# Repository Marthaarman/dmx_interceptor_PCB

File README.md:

# PCB DMX Interceptor
A PCB designed for the dmx-transceiver library, to which an extra switch can be connected.
https://github.com/Marthaarman/dmx-transceiver

schematics: https://github.com/Marthaarman/dmx_interceptor_PCB/blob/main/dmx_interceptor.pdf

## components
- 2x debo rs485 TTL - https://www.reichelt.de/de/en/developer-boards-ttl-to-rs485-max485-debo-rs485-ttl-p282703.html
- 1x arduino pro mini - https://www.digikey.nl/nl/products/detail/sparkfun-electronics/DEV-11113/5140820
- 2x 3 pin screw terminal - https://www.digikey.nl/nl/products/detail/cui-devices/TB009-508-03BE/10064152
- 2x 2 pin screw terminal - https://www.digikey.nl/nl/products/detail/cui-devices/TB009-508-02BE/10064151
- 1x 10k resistor 0603 (1608 metric) - https://www.digikey.nl/nl/products/detail/stackpole-electronics-inc/RNCP0603FTD10K0/2240139
- 2x 12 pin header female - https://www.digikey.nl/nl/products/detail/adam-tech/RS1-12-G/9832041
- 4x 4 pin header female - https://www.digikey.nl/nl/products/detail/adam-tech/RS1-04-G/9829303
- 2x 12 pin header male - https://www.digikey.nl/nl/products/detail/adam-tech/PH1-12-UA/9830395

Depending on the FT232RL you bought you need either male or female:
- 1x female 5 pin header for ft232rl adapter: https://www.digikey.nl/nl/products/detail/adam-tech/RS1-05-G/9832046
- 1x male 5 pin header for ft232rl adapter: https://www.digikey.nl/nl/products/detail/adam-tech/PH1RB-05-UA/9831540

### 1 time requirement: 	
- 1x FT232RL USB TTL Serial Port Adapter 3.3v/5V - https://www.digikey.nl/nl/products/detail/sparkfun-electronics/KIT-18290/14552423

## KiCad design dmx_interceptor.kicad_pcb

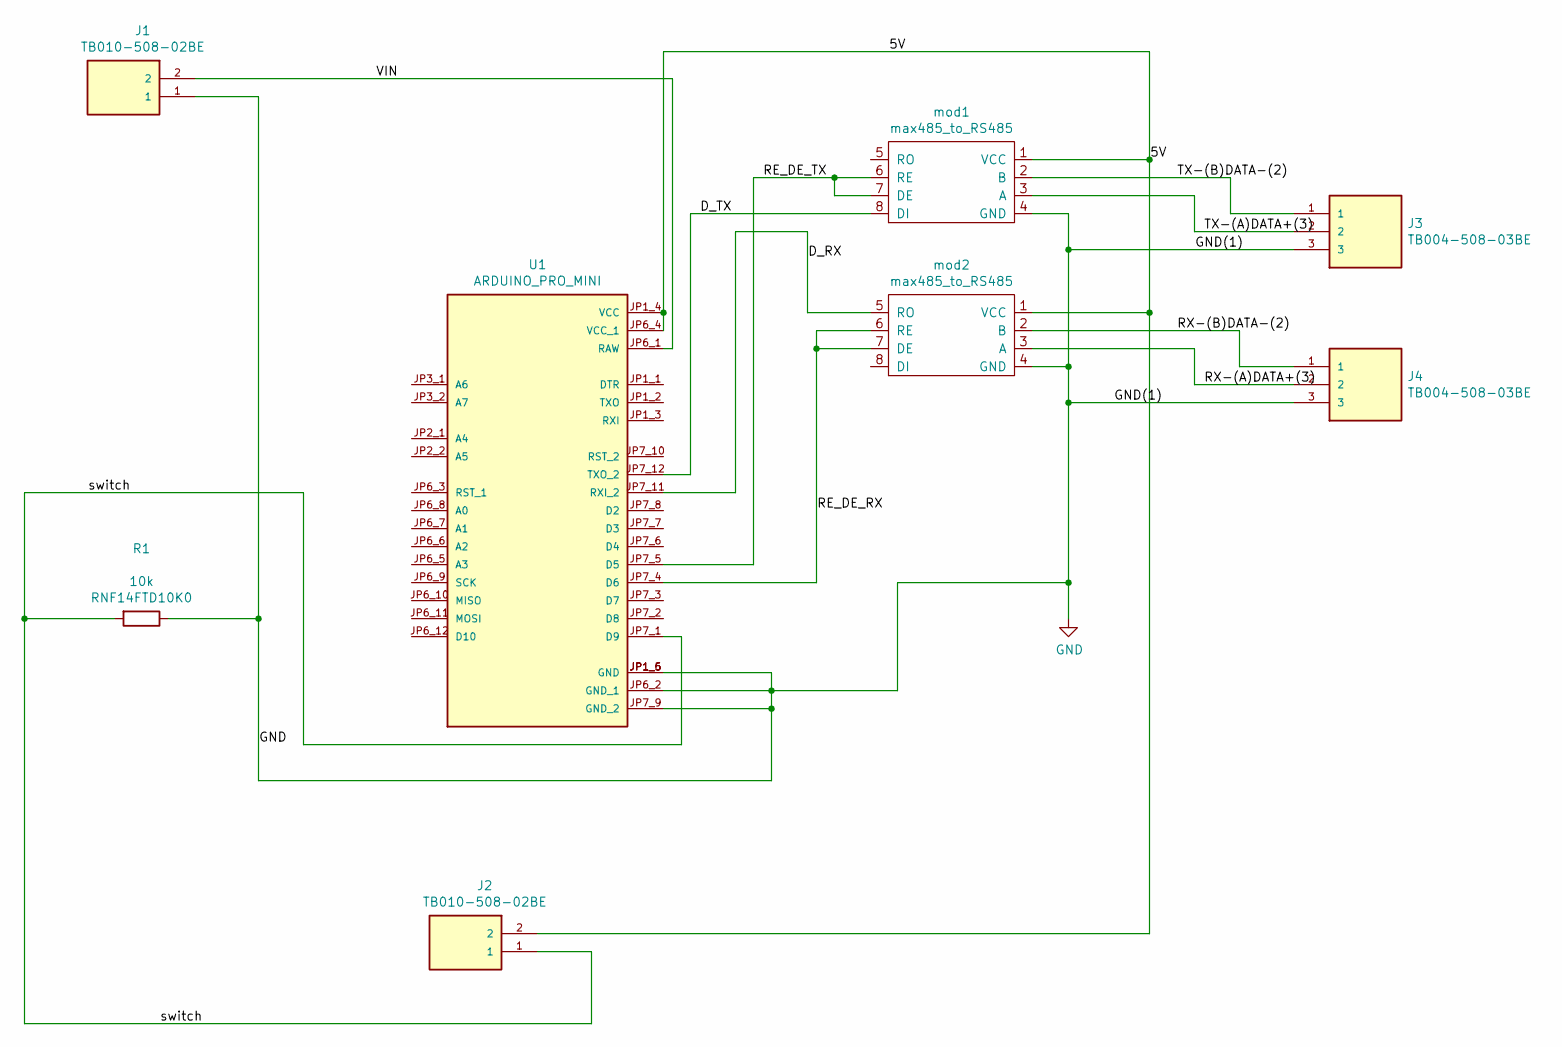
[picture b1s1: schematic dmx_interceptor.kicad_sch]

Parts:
J1, J2: TB010-508-02BE; CUI_TB010-508-02BE; MPN TB010-508-02BE
J3, J4: TB004-508-03BE; CUI_TB004-508-03BE; mpn TB004-508-03BE
R1: R-generic; R_THT; MPN RNF14FTD10K0
U1: ARDUINO_PRO_MINI; MODULE_ARDUINO_PRO_MINI; PARTREV N/A
mod1, mod2: max485_to_RS485; max485_to_rs485

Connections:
/5V: J2.2, U1.JP1_4 (VCC), U1.JP6_4 (VCC_1), mod1.1 (VCC), mod2.1 (VCC)
/D_RX: U1.JP7_11 (RXI_2), mod2.5 (RO)
/D_TX: U1.JP7_12 (TXO_2), mod1.8 (DI)
/RE_DE_RX: U1.JP7_4 (D6), mod2.6 (RE), mod2.7 (DE)
/RE_DE_TX: U1.JP7_5 (D5), mod1.6 (RE), mod1.7 (DE)
/RX-(A)DATA+(3): J4.2, mod2.3 (A)
/RX-(B)DATA-(2): J4.1, mod2.2 (B)
/TX-(A)DATA+(3): J3.2, mod1.3 (A)
/TX-(B)DATA-(2): J3.1, mod1.2 (B)
/VIN: J1.2, U1.JP6_1 (RAW)
/switch: J2.1, R1.2, U1.JP7_1 (D9)
GND: J1.1, J3.3, J4.3, R1.1, U1.JP1_5 (GND), U1.JP1_6 (GND), U1.JP6_2 (GND_1), U1.JP7_9 (GND_2), mod1.4 (GND), mod2.4 (GND)

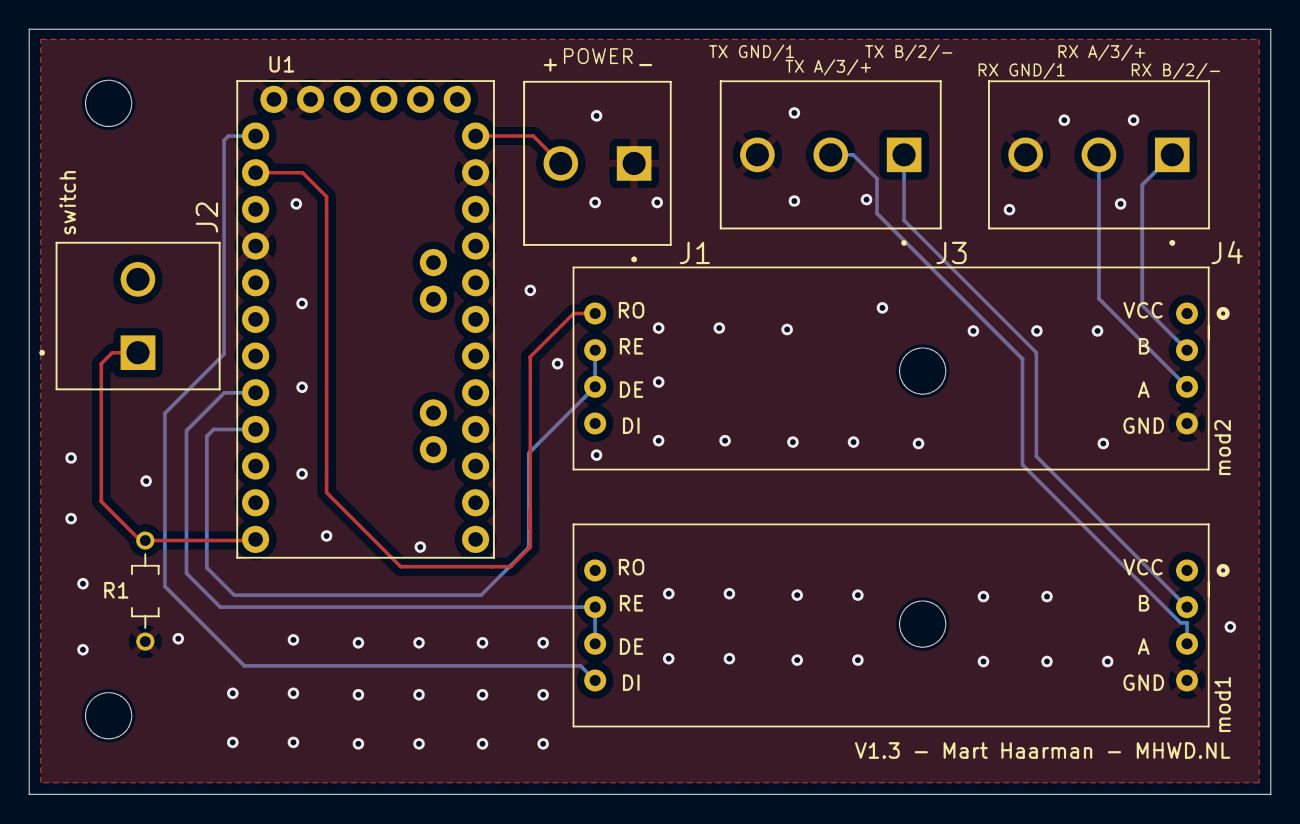
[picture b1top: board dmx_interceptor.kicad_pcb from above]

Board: 4 copper layers, 86.0 x 53.0 mm, 8 parts (0 on the bottom side), 12 nets.

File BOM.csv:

"Reference","Value","Footprint","Datasheet","MANUFACTURER","MAXIMUM_PACKAGE_HEIGHT","MPN","Manufacturer","Manufacturer Part Link","PARTREV","Resistance","STANDARD","Qty"
"J1, J2","TB010-508-02BE","dmx_interceptor:CUI_TB010-508-02BE","","CUI","","TB010-508-02BE","","","","","Manufacturer Recommendations","2"
"J3, J4","TB004-508-03BE","dmx_interceptor:CUI_TB004-508-03BE","","CUI","","TB004-508-03BE","","","","","Manufacturer Recommendations","2"
"mod1, mod2","max485_to_RS485","dmx_interceptor:max485_to_rs485","","","","","","","","","","2"
"R1","R-generic","dmx_interceptor:smd_0603_1608-Metric","~","","","RNCP0603FTD10K0","","","","10k","","1"
"U1","ARDUINO_PRO_MINI","dmx_interceptor:MODULE_ARDUINO_PRO_MINI","","SparkFun Electronics","N/A","DEV-11113","","","N/A","","Manufacturer Recommendations","1"

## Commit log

2022-10-13 init
2022-10-13 Create LICENSE
2023-02-21 fix all refs
2023-02-23 output files for ordering & pcb fix
2023-02-23 new readme
2023-04-13 change resistor to throughole
2023-05-24 added 4 mounting holes
